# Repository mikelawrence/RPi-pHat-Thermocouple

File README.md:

# Raspberry Pi Thermocouple pHat

The Raspberry Pi Zero sized Hats are now officially called **Micro-Hats** or **uHats** but for consistency sake, this board's name will remain Raspberry Pi Thermocouple **pHat**.

This is a Raspberry Pi Micro-Hat PCB that supports:

* Three MAX31850 1-Wire Thermocouple Converters for remote temperature sensing
* DS18S20 1-Wire Thermometer for local Hat temperature
* Magnetic Buzzer/Alert

I keep an upright freezer in my garage and on two occasions I have had the freezer die without getting noticed for several days. This project is an attempt to solve my lack of constant oversight. MQTT is used to communicate with Home Assistant home automation software. The MQTT client/server model is very effective in this situation. Home Assistant will monitor the temperature and provide me with alerts so I can do something about the problem before all the food spoils.

## Status

* Rev 2.0 PCB has been ordered from OSH Park and has been fully tested.
  * Removed one of the four MAX31850K's.
  * Increased thermocouple input filtering by adding ferrite beads and a larger capacitor.
  * Added DC Power connector and switching power supply that powers both the Raspberry Pi and the Hat.
  * The occasional noisy reading from the MAX31850K's are reduced in this version but not gone.
  * You can order parts from Mouser using this [shared BOM](https://www.mouser.com/ProjectManager/ProjectDetail.aspx?AccessID=bd69c35967).
  * You can order the PCB from OSH Park using this [link](https://oshpark.com/shared_projects/meYar6Ji).
* Rev 1.2 PCB has been ordered from OSH Park and tested.
  * Discovered the MAX31850K's get a noisy reading about 0.1% of the time. This noise is typically within 5 C but sometimes is greater than 30 C. Adding capacitors did little to help the Rev 1.1 design so most of the 3.3V power was switched to a 3.3V LDO regulator in an attempt to reduce the noise on the 3.3V power seen by the MAX31850K's.
  * You can order parts from Mouser using this [shared BOM](http://www.mouser.com/ProjectManager/ProjectDetail.aspx?AccessID=7612d46eeb).
  * You can order the PCB from OSH Park using this [link](https://oshpark.com/shared_projects/S5a4ZDvw).
* Rev 1.1 PCB was never built.
  * Added a pulldown on the alert signal to prevent the Alert buzzer from sounding on power on.
  * Added an on board DS18S20.
* Rev 1.0 PCB has been ordered from OSH Park and tested.
  * Discovered the linux kernel doesn't seem to support MAX31850K devices without a DS18S20 present. The kernel detects the MAX31850K devices but does not create a w1_slave file to read the temperature. This is most likely a bug in the Linux W1 driver.

## Board Preview

## Kicad Notes

* This PCB design uses my custom libraries available here [Mike's KiCad Libraries](https://github.com/mikelawrence/KiCad-Libraries).
* This PCB design is based on [RPi_Zero_pHat_Template](https://github.com/mikelawrence/RPi_Zero_pHat_Template).
* This PCB was designed with [KiCad 5.1.2](http://kicad.org).
* For Bill of Materials generation I use my version of [KiBoM](https://github.com/mikelawrence/KiBoM) forked from [SchrodingersGat](https://github.com/SchrodingersGat/KiBoM).
* The LMZ21700 Simple Switcher, AT24CS32, and MAX31850K parts have an exposed pad on the bottom which requires either a reflow oven or hot air to solder properly.

## Design

### Input Power

This Hat will safely power the Raspberry Pi and this board up to 650mA. Keep in mind that 650mA is not enough for the minimum specified backpower of 1.3A. It is however enough to power (with room to spare) a Raspberry Pi Zero W with nothing else connected. The Barrel Jack will accept 6-11VAC or 6-17VDC. This input voltage is rectified and filtered and applied to a 5VDC Simpler Switcher module from Texas Instruments (LMZ21700). The output of this switcher is applied to the Raspberry Pi 5V through an ideal diode circuit which will prevent any problems when both the Hat and Raspberry Pi are powered simultaneously.

### MAX31850K Thermocouple-to-Digital Converter

Although the MAX38150K datasheet typical application circuit doesn't show the use of ferrite beads many designs seem to include them. That in combination with the larger than normal capacitor across the input will hopefully improve sampling errors even further.

## Raspberry Pi Setup

This setup makes several assumptions. First you are using Raspbian Buster. This software and instructions most likely work on other versions of Raspbian but they have not been tested. Second Python3 is the target programming environment. It is also assumed that you are using the standard `pi` user. Otherwise you will have to edit the commands by replacing `/home/pi` with your user's home directory. Install everything needed by executing the following commands.

```text
sudo apt update
sudo apt -y install git python3-rpi.gpio python3-w1thermsensor python3-paho-mqtt
```

### Get the repository from Github

Clone this repository from Github with the following commands.

```text
cd /home/pi
git clone https://github.com/mikelawrence/RPi-pHat-Thermocouple
```

### Configure ID EEPROM

Raspberry Pi Hats require an ID EEPROM with data that uniquely identifies every hat ever made. Build the EEPROM tools, and make the `eeprom_settings.eep` file.

```text
cd /home/pi/RPi-pHat-Thermocouple/eeprom/
make all
./eepmake eeprom_settings.txt eeprom_settings.eep
```

The next command writes the freshly generated and unique `eeprom_settings.eep` file to the EEPROM but you must push and hold the write switch on the hat before executing this command. By default the EEPROM on the hat is write protected. Pushing the write switch allows writes to occur while the switch is pushed.

```text
chmod 755 eepflash.sh
sudo ./eepflash.sh -w -f=eeprom_settings.eep -t=24c32
```

You will see the following if writing to the EEPROM was successful.

```text
This will attempt to talk to an EEPROM at i2c address 0x50. Make sure there is an EEPROM at this address.
This script comes with ABSOLUTELY no warranty. Continue only if you know what you are doing.
Do you wish to continue? (yes/no): yes
Writing...
0+1 records in
0+1 records out
117 bytes (117 B) copied, 2.31931 s, 0.1 kB/s
Done.
```

This is what you will see if there is a problem communicating with the EEPROM.

```text
This will attempt to talk to an EEPROM at i2c address 0x50. Make sure there is an EEPROM at this address.
This script comes with ABSOLUTELY no warranty. Continue only if you know what you are doing.
Do you wish to continue? (yes/no): yes
Writing...
dd: error writing ‘/sys/class/i2c-adapter/i2c-3/3-0050/eeprom’: Connection timed out
0+1 records in
0+0 records out
0 bytes (0 B) copied, 0.0539977 s, 0.0 kB/s
Error doing I/O operation.
```

If you successfully wrote the EEPROM there is nothing else left to do here.

### Setup Interfaces

For this Hat you will need to enable the 1-Wire interface. From the command line type
`sudo raspi-config` and follow the prompts to install  support in the kernel.

It's time to reboot your Raspberry Pi with `sudo reboot`.

### Test the 1-Wire Temperature Sensors

[Python3-w1thermsensor](https://github.com/timofurrer/w1thermsensor) is a nice 1-Wire python library that also supports command line reading of temperatures from 1-Wire devices. You should have already installed this package in the [Raspberry Pi Setup](#Raspberry-Pi-Setup) section.

Test the single on-board DS18B20 temperature sensor using `w1thermsensor all --type DS18S20`.

```text
pi@studio-fridge:~ $ w1thermsensor all --type DS18S20
Got temperatures of 1 sensors:
  Sensor 1 (00080372f2c4) measured temperature: 28.06 celsius
```

Now test the three MAX38150Ks temperature sensor by using `w1thermsensor all --type MAX31850K`.

```text
pi@studio-fridge:~ $ w1thermsensor all --type MAX31850K
Got temperatures of 3 sensors:
  Sensor 1 (000000181928) measured temperature: 23.75 celsius
  Sensor 2 (00000018192b) measured temperature: 24.0 celsius
  Sensor 3 (000000181d59) measured temperature: 2047.81 celsius
```

The 2047.81 celsius reading is what you get when there is no thermocouple connected to the MAX31850K.

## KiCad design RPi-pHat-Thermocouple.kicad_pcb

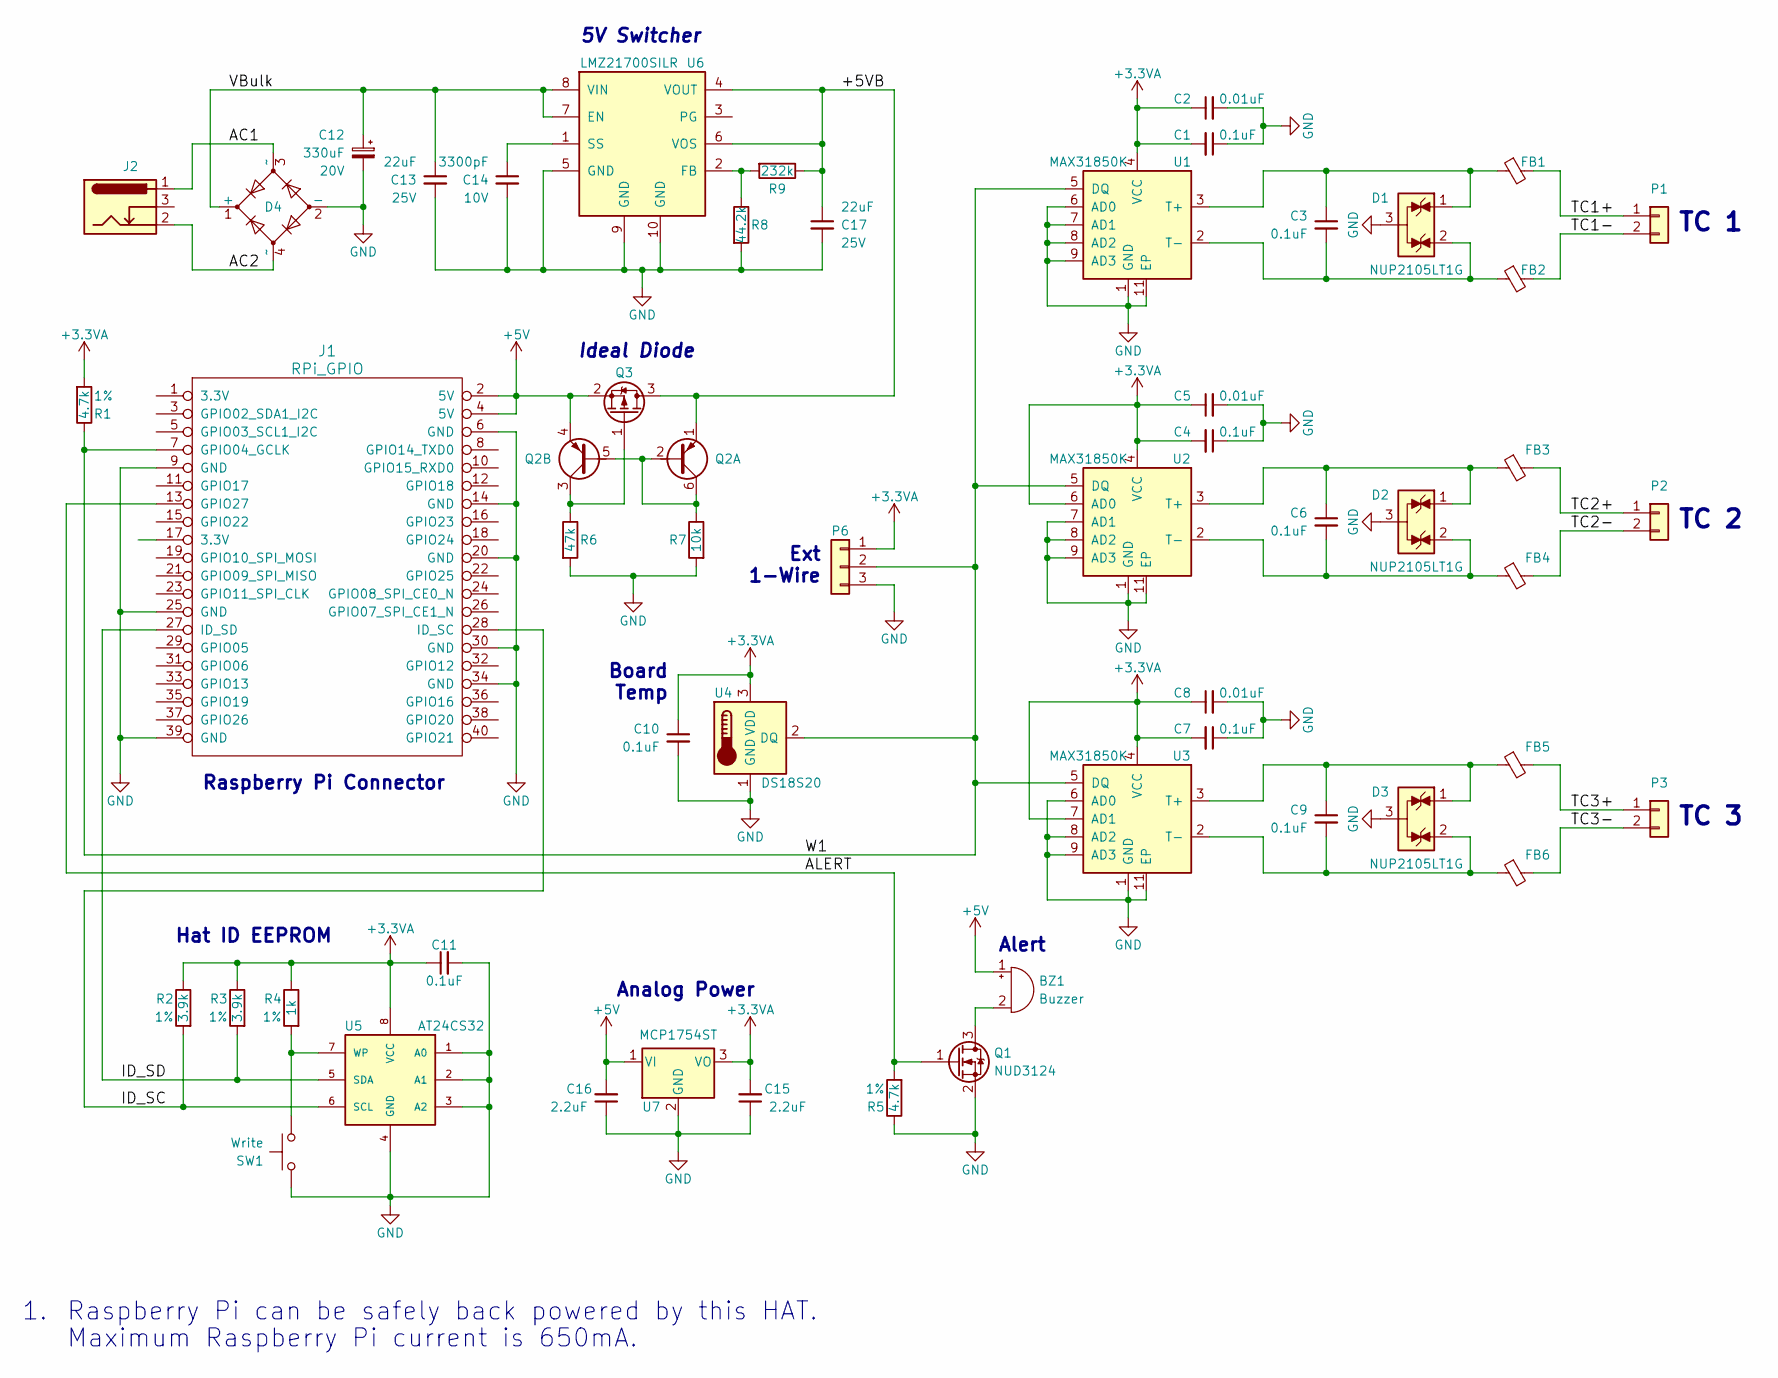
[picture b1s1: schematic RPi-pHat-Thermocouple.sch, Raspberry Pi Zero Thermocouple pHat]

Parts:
BZ1: Buzzer; MagneticBuzzer_CUI-CMI-9655S; Part Number CMI-9655S-SMT-TR
C1, C3, C4, C6, C7, C9, C10, C11: 0.1uF; C_0603_1608Metric; Part Number CC0603KRX7R9BB104
C2, C5, C8: 0.01uF; C_0603_1608Metric; Part Number CC0603KRX7R9BB103
C12: 330uF; CP_Elec_10x7.9; Voltage 20V; Tolerance 20%; Part Number PCR1D331MCL1GS
C13, C17: 22uF; C_0805_2012Metric; Voltage 25V; Tolerance 20%; Part Number TMK212BBJ226MG-TT
C14: 3300pF; C_0603_1608Metric; Voltage 10V; Tolerance 5%; Part Number VJ0603Y332JXQPW1BC
C15, C16: 2.2uF; C_0805_2012Metric; Part Number CC0805KKX7R7BB225
D1, D2, D3: NUP2105LT1G; SOT-23; Part Number NUP2105LT1G
D4: Diode_Bridge_Vishay_DFS; Part Number DF206ST-G
FB1, FB2, FB3, FB4, FB5, FB6: 1k; L_0603_1608Metric; Part Number MMZ1608B102CTD25
J1: RPi_GPIO; PinSocket_2x20_P2.54mm_Vertical; Part Number 2222
J2: Barrel_Jack_Switch; BarrelJack_CUI_PJ-036AH-SMT_Horizontal; Part Number PJ-036AH-SMT-TR
P1, P2, P3: CONN_01X02; Pin_Header_Straight_1x02_Pitch2.54mm
P6: CONN_01X03; Pin_Header_Straight_1x03_Pitch2.00mm
Q1: NUD3124; SOT-23; Part Number NUD3124LT1G
Q2: BCM857BS; SOT-363_SC-70-6; Part Number BCM857BS-7-F
Q3: DMG2305UX; SOT-23; Part Number DMG2305UX-7
R1, R5: 4.7k; R_0603_1608Metric; Tolerance 1%; Part Number ERJ-3EKF4701V
R2, R3: 3.9k; R_0603_1608Metric; Tolerance 1%; Part Number ERJ-3EKF3901V
R4: 1k; R_0603_1608Metric; Tolerance 1%; Part Number ERJ-3EKF1001V
R6: 47k; R_0603_1608Metric; Tolerance 1%; Part Number ERJ-3EKF4702V
R7: 10k; R_0603_1608Metric; Tolerance 1%; Part Number ERJ-3EKF1002V
R8: 44.2k; R_0603_1608Metric; Tolerance 1%; Part Number ERJ-3EKF4422V
R9: 232k; R_0603_1608Metric; Tolerance 1%; Part Number RC0603FR-07232KL
SW1: Write; SW_SPST_B3U-1000P; Part Number B3U-1000P
U1, U2, U3: MAX31850K; TDFN-10-1EP_3x4mm_Pitch0.5mm; Part Number MAX31850KATB+
U4: DS18S20; TO-92; Part Number DS18S20+
U5: AT24CS32; DFN-8-1EP_3x2mm_P0.5mm_EP1.3x1.5mm; Part Number AT24CS32-MAHM-E
U6: LMZ21700; Converter_DCDC_Texas-SIL0008E; Part Number LMZ21700SILR
U7: MCP1754ST; SOT-89-3; Part Number MCP1754ST-3302E/MB

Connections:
+3.3VA: C1.2, C2.1, C4.2, C5.1, C7.2, C8.1, C10.1, C11.1, C15.2, P6.1, R1.2, R2.1, R3.1, R4.1, U1.4 (VCC), U2.4 (VCC), U2.6 (AD0), U3.4 (VCC), U3.7 (AD1), U4.3 (VDD), U5.8 (VCC), U7.3 (VO)
+5V: BZ1.1 (-), C16.2, J1.2 (5V), J1.4 (5V), Q2.4 (E2), Q3.2 (S), U7.1 (VI)
/+5VB: C17.1, Q2.1 (E1), Q3.3 (D), R9.1, U6.4 (VOUT), U6.6 (VOS)
/AC1: D4.3 (~~), J2.1
/AC2: D4.4 (~~), J2.2
/ALERT: J1.13 (GPIO27), Q1.1 (G), R5.2
/ID_SC: J1.28 (ID_SC), R2.2, U5.6 (SCL)
/ID_SD: J1.27 (ID_SD), R3.2, U5.5 (SDA)
/TC1+: FB1.2, P1.1
/TC1-: FB2.2, P1.2
/TC2+: FB3.2, P2.1
/TC2-: FB4.2, P2.2
/TC3+: FB5.2, P3.1
/TC3-: FB6.2, P3.2
/VBulk: C12.1, C13.1, D4.1 (+), U6.7 (EN), U6.8 (VIN)
/W1: J1.7 (GPIO04_GCLK), P6.2, R1.1, U1.5 (DQ), U2.5 (DQ), U3.5 (DQ), U4.2 (DQ)
GND: C1.1, C2.2, C4.1, C5.2, C7.1, C8.2, C10.2, C11.2, C12.2, C13.2, C14.2, C15.1, C16.1, C17.2, D1.3 (A), D2.3 (A), D3.3 (A), D4.2 (-), J1.6 (GND), J1.9 (GND), J1.14 (GND), J1.20 (GND), J1.25 (GND), J1.30 (GND), J1.34 (GND), J1.39 (GND), P6.3, Q1.2 (S), R5.1, R6.2, R7.2, R8.2, SW1.1, U1.1 (GND), U1.6 (AD0), U1.7 (AD1), U1.8 (AD2), U1.9 (AD3), U1.11 (EP), U2.1 (GND), U2.7 (AD1), U2.8 (AD2), U2.9 (AD3), U2.11 (EP), U3.1 (GND), U3.6 (AD0), U3.8 (AD2), U3.9 (AD3), U3.11 (EP), U4.1 (GND), U5.1 (A0), U5.2 (A1), U5.3 (A2), U5.4 (GND), U6.5 (GND), U6.9 (GND), U6.10 (GND), U7.2 (GND)
unnamed: BZ1.2 (+), Q1.3 (D)
unnamed: C3.1, D1.1 (K), FB1.1, U1.3 (T+)
unnamed: C3.2, D1.2 (K), FB2.1, U1.2 (T-)
unnamed: C6.1, D2.1 (K), FB3.1, U2.3 (T+)
unnamed: C6.2, D2.2 (K), FB4.1, U2.2 (T-)
unnamed: C9.1, D3.1 (K), FB5.1, U3.3 (T+)
unnamed: C9.2, D3.2 (K), FB6.1, U3.2 (T-)
unnamed: C14.1, U6.1 (SS)
unnamed: Q2.2 (B1), Q2.5 (B2), Q2.6 (C1), R7.1
unnamed: Q2.3 (C2), Q3.1 (G), R6.1
unnamed: R4.2, SW1.2, U5.7 (WP)
unnamed: R8.1, R9.2, U6.2 (FB)

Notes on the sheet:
Hat ID EEPROM
TC 1
TC 2
TC 3
Analog Power
Board Temp
5V Switcher
Ideal Diode
Raspberry Pi Connector
Ext 1-Wire
Alert
Raspberry Pi can be safely back powered by this HAT.
Maximum Raspberry Pi current is 650mA.

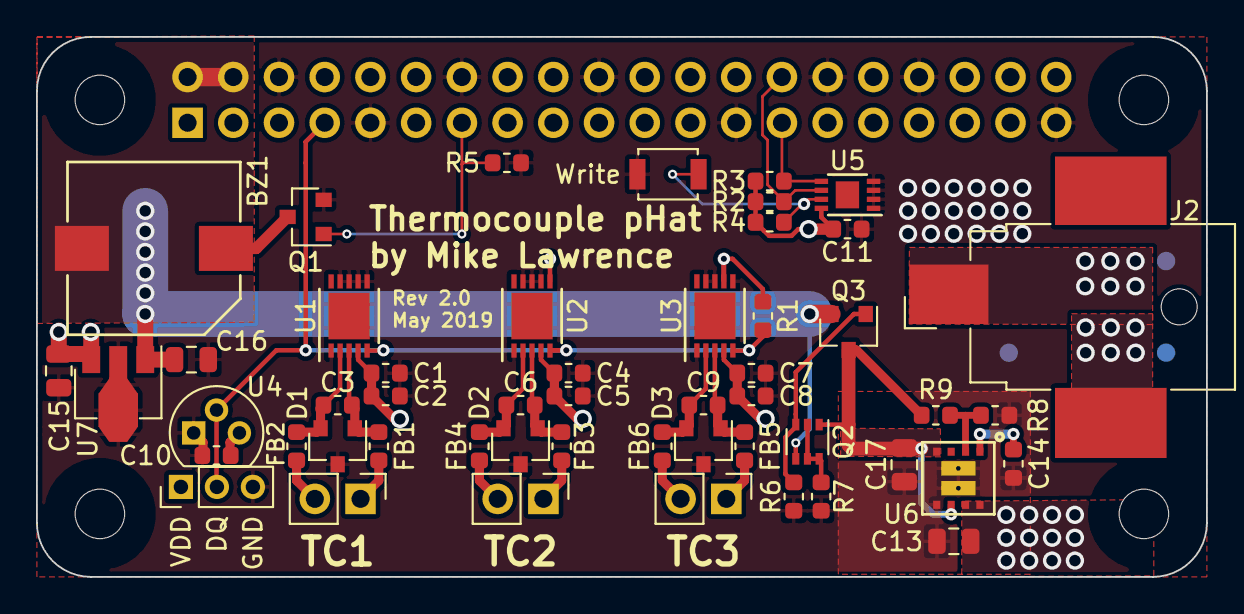
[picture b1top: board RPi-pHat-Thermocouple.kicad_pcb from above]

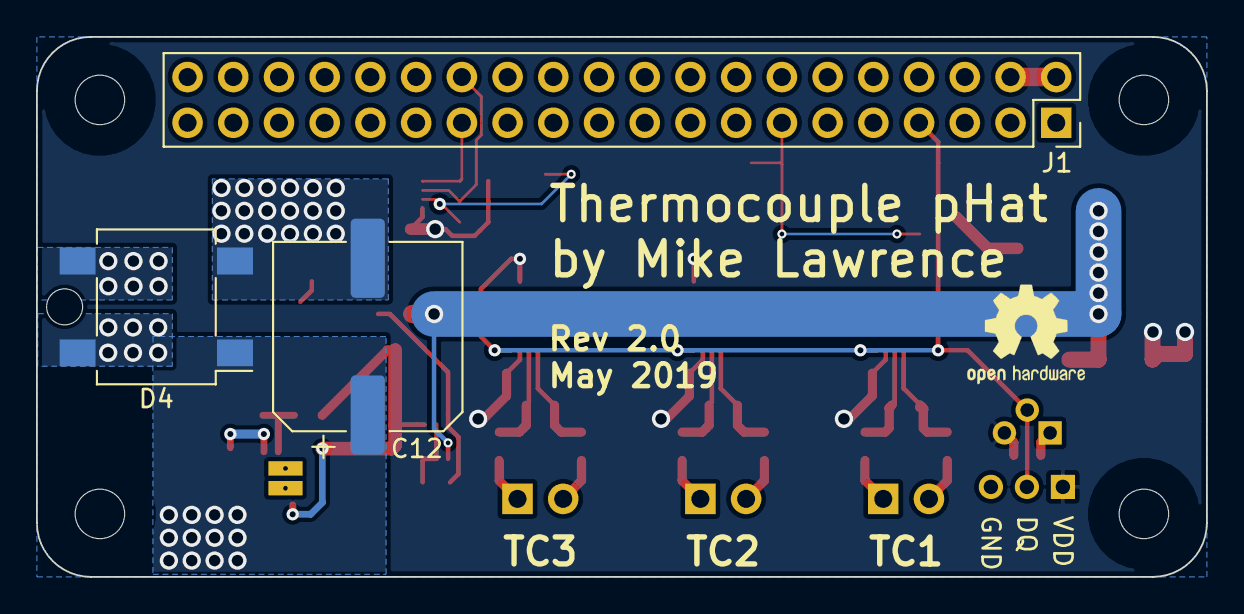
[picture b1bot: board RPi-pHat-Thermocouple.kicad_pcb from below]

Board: 2 copper layers, 65.0 x 30.0 mm, 54 parts (3 on the bottom side), 29 nets.

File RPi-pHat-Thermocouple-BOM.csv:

Quantity,References,Description,Manufacturer,Part Number,Vendor,Vendor Part Number
1,BZ1,"BUZ, SMD, 2.7kHz, 5V, 30mA",CUI,CMI-9655S-SMT-TR,Mouser,490-CMI-9655S-SMT-TR
8,C1 C3 C4 C6 C7 C9 C10 C11,"CAP, 0603, .1uF, 10%, X7R, 50V",Yageo,CC0603KRX7R9BB104,Mouser,603-CC603KRX7R9BB104
3,C2 C5 C8,"CAP, 0603, .01uF, 10%, X7R, 50V",Murata Electronics,CC0603KRX7R9BB103,Mouser,603-CC603KRX7R9BB103
1,C12,"CAP, SMD10X8, 330uF, 20%, EC, 20V",Nichicon,PCR1D331MCL1GS,Mouser,647-PCR1D331MCL1GS
2,C13 C17,"CAP, 0805, 22uf, 20%, X5R, 25V",Taiyo Yuden,TMK212BBJ226MG-TT,Mouser,963-TMK212BBJ226MGTT
1,C14,"CAP, 0603, 3300pF, 5%, X7R, 10V",Vishay,VJ0603Y332JXQPW1BC,Mouser,77-VJ0603Y332JXQPBC
2,C15 C16,"CAP, 0805, 2.2uF, 10%, X7R, 16V",Yageo,CC0805KKX7R7BB225,Mouser,603-CC805KKX7R7BB225
3,D1 D2 D3,"TVS, SOT23, ESD TVS Protection",On Semi,NUP2105LT1G,Mouser,863-NUP2105LT1G
1,D4,"DIODE, DFS, Bridge Diode, 2A, 600V",Comchip,DF206ST-G,Mouser,750-DF206ST-G
6,FB1 FB2 FB3 FB4 FB5 FB6,"BEAD, 0603, .3A, 1k@100MHz",TDK,MMZ1608B102CTD25,Mouser,810-MMZ1608B102CTD25
1,J1,"CON, THT, Dual Row Socket, 2.54mm, 40 Pos",Adafruit,2222,Mouser,485-2222
1,J2,"CON, SMD, Barrel Jack, 2.0mm center",CUI,PJ-036AH-SMT-TR,Mouser,490-PJ-036AH-SMT-TR
1,Q1,"IC, SOT23, Inductive Load Driver",On Semi,NUD3124LT1G,Mouser,863-NUD3124LT1G
1,Q2,"TRANSISTOR, SOT363, Bipolar, PNP, Dual Matched",Diodes Inc,BCM857BS-7-F,Mouser,621-BCM857BS-7-F
1,Q3,"TRANSISTOR, SOT23, Mosfet, P-CH, -5A, -20V",Diodes Inc,DMG2305UX-7,Mouser,621-DMG2305UX-7
2,R1 R5,"RES, 0603, 4.7k, 1%, T100",Panasonic,ERJ-3EKF4701V,Mouser,667-ERJ-3EKF4701V
2,R2 R3,"RES, 0603, 3.9k, 1%, T100",Panasonic,ERJ-3EKF3901V,Mouser,667-ERJ-3EKF3901V
1,R4,"RES, 0603, 1k, 1%, T100",Panasonic,ERJ-3EKF1001V,Mouser,667-ERJ-3EKF1001V
1,R6,"RES, 0603, 47k, 1%, T100",Panasonic,ERJ-3EKF4702V,Mouser,667-ERJ-3EKF4702V
1,R7,"RES, 0603, 10k, 1%, T100",Panasonic,ERJ-3EKF1002V,Mouser,667-ERJ-3EKF1002V
1,R8,"RES, 0603, 44.2k, 1%, T100",Panasonic,ERJ-3EKF4422V,Mouser,667-ERJ-3EKF4422V
1,R9,"RES, 0603, 232k, 1%, T100",Yageo,RC0603FR-07232KL,Mouser,603-RC0603FR-07232KL
1,SW1,"SW, SMD, Push Button",Omron,B3U-1000P,Mouser,653-B3U-1000P
3,U1 U2 U3,"IC, TDFN10, 1-Wire Thermocouple Converter",Maxim,MAX31850KATB+,Mouser,700-MAX31850KATB+
1,U4,"IC, TO92, 1-Wire Temperature Sensor",Maxim,DS18S20+,Mouser,700-DS18S20
1,U5,"IC, DFN8, I2C Serial EEPROM, 32kbit",Atmel,AT24CS32-MAHM-E,Mouser,556-AT24CS32-MAHM-E
1,U6,"MODULE, SMD, Simple Switcher, 17V, .65A",TI,LMZ21700SILR,Mouser,595-LMZ21700SILR
1,U7,"IC, SOT89-3, LDO VREG, 16V, .15A",Microchip,MCP1754ST-3302E/MB,Mouser,579-MCP1754ST3302EMB

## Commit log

2017-03-17 Added .gitignore and BOM
2017-03-17 Add Mouser BOM link
2017-03-17 Updated schematic parts fields on MAX31850k parts.
2017-03-17 Delete RPi-pHat-Thermocouple.kicad_pcb-bak
    No reason to keep this file on GIT
2017-03-17 Minor README changes
2017-03-17 Add note about MAX31850 package
2017-03-17 Delete RPi-pHat-Thermocouple.bak
    No need to keep this file in GIT
2017-03-17 Added solder paste gerber for stencils.
2017-03-26 Status update in README file
2017-03-26 Added U2 and R5
    Fixed Alert sounding as soon as power is applied by adding pulldown
    (R5). Added Ds18S20 (U2) so the Linux kernel will properly access the
    MAX31850K.
2017-03-26 Minor correction to README
2017-03-26 Cleanup Fab layer
2017-04-07 Added Analog Power Supply
2017-04-08 Changed EEPROM setting to support new Rev 1.2
2017-04-14 Correct Title Block Date and Revision
2017-08-19 Quick title change
2019-05-21 Remove one MAX38150K add switching power supply
    Removed one MAX38150K so now there are three on the board.
    Added switching power supply to safely backpower the Raspberry Pi Zero.
    Now has Barrel Jack for input power.
    Updated schematic BOM fields and added KiBOM support.
2019-06-27 Added Fridge Monitor application in python. Updated READMEs.
2019-06-27 Update READMEs.
2019-06-29 Add MQTT authentication.
    Fix configuration file defaults not working.
    PEP8 formatting.
2019-07-01 pHat is now uHat. Added check for correct Hat connected.
2019-07-01 Reverted uHat to pHat to prevent confusion
2019-07-02 Now using python logging.
2019-07-02 Delete tempdata.cpython-37.pyc
    Remove accidental add.
2019-07-02 Delete timer.cpython-37.pyc
    Remove accidental add.
2019-07-02 Delete .DS_Store
    Remove accidental add.
2019-07-02 Delete ._.DS_Store
    Remove accidental add.
2019-07-02 Delete tempdata.py
    Remove accidental add.
2019-07-02 Convert to python logging.
2019-07-02 Delete eepdump
    Remove accidental add.
2019-07-02 Delete eepmake
    Remove accidental add.
2019-07-02 Delete eeprom_settings.eep
    Remove accidental add.
2019-07-05 NIST thermocouple linearization refactor. Working good now.
    Add Enable_RSSI in config.
    Add more error checking in measureSensors().
2019-07-13 First operational version of Fridge Monitor.
    Thermocouple linearization now works.
    Temperature data class (tempdata) now supports 1 minute and 24 hour averaging, alarms, write/read sample data to/from files to prevent data loss on averages.
    Verifies correct Hat is connected.
    Detects door open/close with temperature only.
2019-09-02 Update README.md
    OSHPark link now correctly point to Rev 2.0 of the design. Fix issue #2.
    Update package install command.
2019-09-02 Fix README package command line.
2019-12-27 Fix data file loading error when missing.
    Minor changes to README file.
    Comment out some testing code.
2020-02-04 Add better Home Assistant Discovery support.
2021-11-08 Update README.md
    https://forum.kicad.info/t/warning-avoid-all-links-to-kicad-pcb-org-use-kicad-org/31521
